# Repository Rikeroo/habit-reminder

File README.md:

# Habit Reminder
Low energy physical habit reminder, using RGB LEDs, a small task screen and tactile switches to build useful habits and get tasks done

## DevBoard Prototype:

## ESP-32 WROOM Board Render:

## Features
- OLED screen to display tasks
- NeoPixel WS281b LED modules to show completion at a glance
- Tactile buttons to complete tasks
## Planned Features
- Integration with ToDoist API, with 2-way sync
- FreeRTOS Implementation for easy scheduling
- Speaker for audible task complete sound
- Enclosure/Stand for flexible display options
- Points/Streaks counter
- LED Integrated buttons? (RBG mech switches)

## Learnt from DevBoard V1 Manufacture and build
- WS2812b fine with 5V supply and 3.3V logic
- Status LED would be usefull for de-bugging
- 4 Pin Female socket for screen would make build easier
- Feet required, or Command strip mounting, or enclosure
- Moving NeoPixels away from screen would make for easier soldering
- Add mounting holes to main pcb for enclosure

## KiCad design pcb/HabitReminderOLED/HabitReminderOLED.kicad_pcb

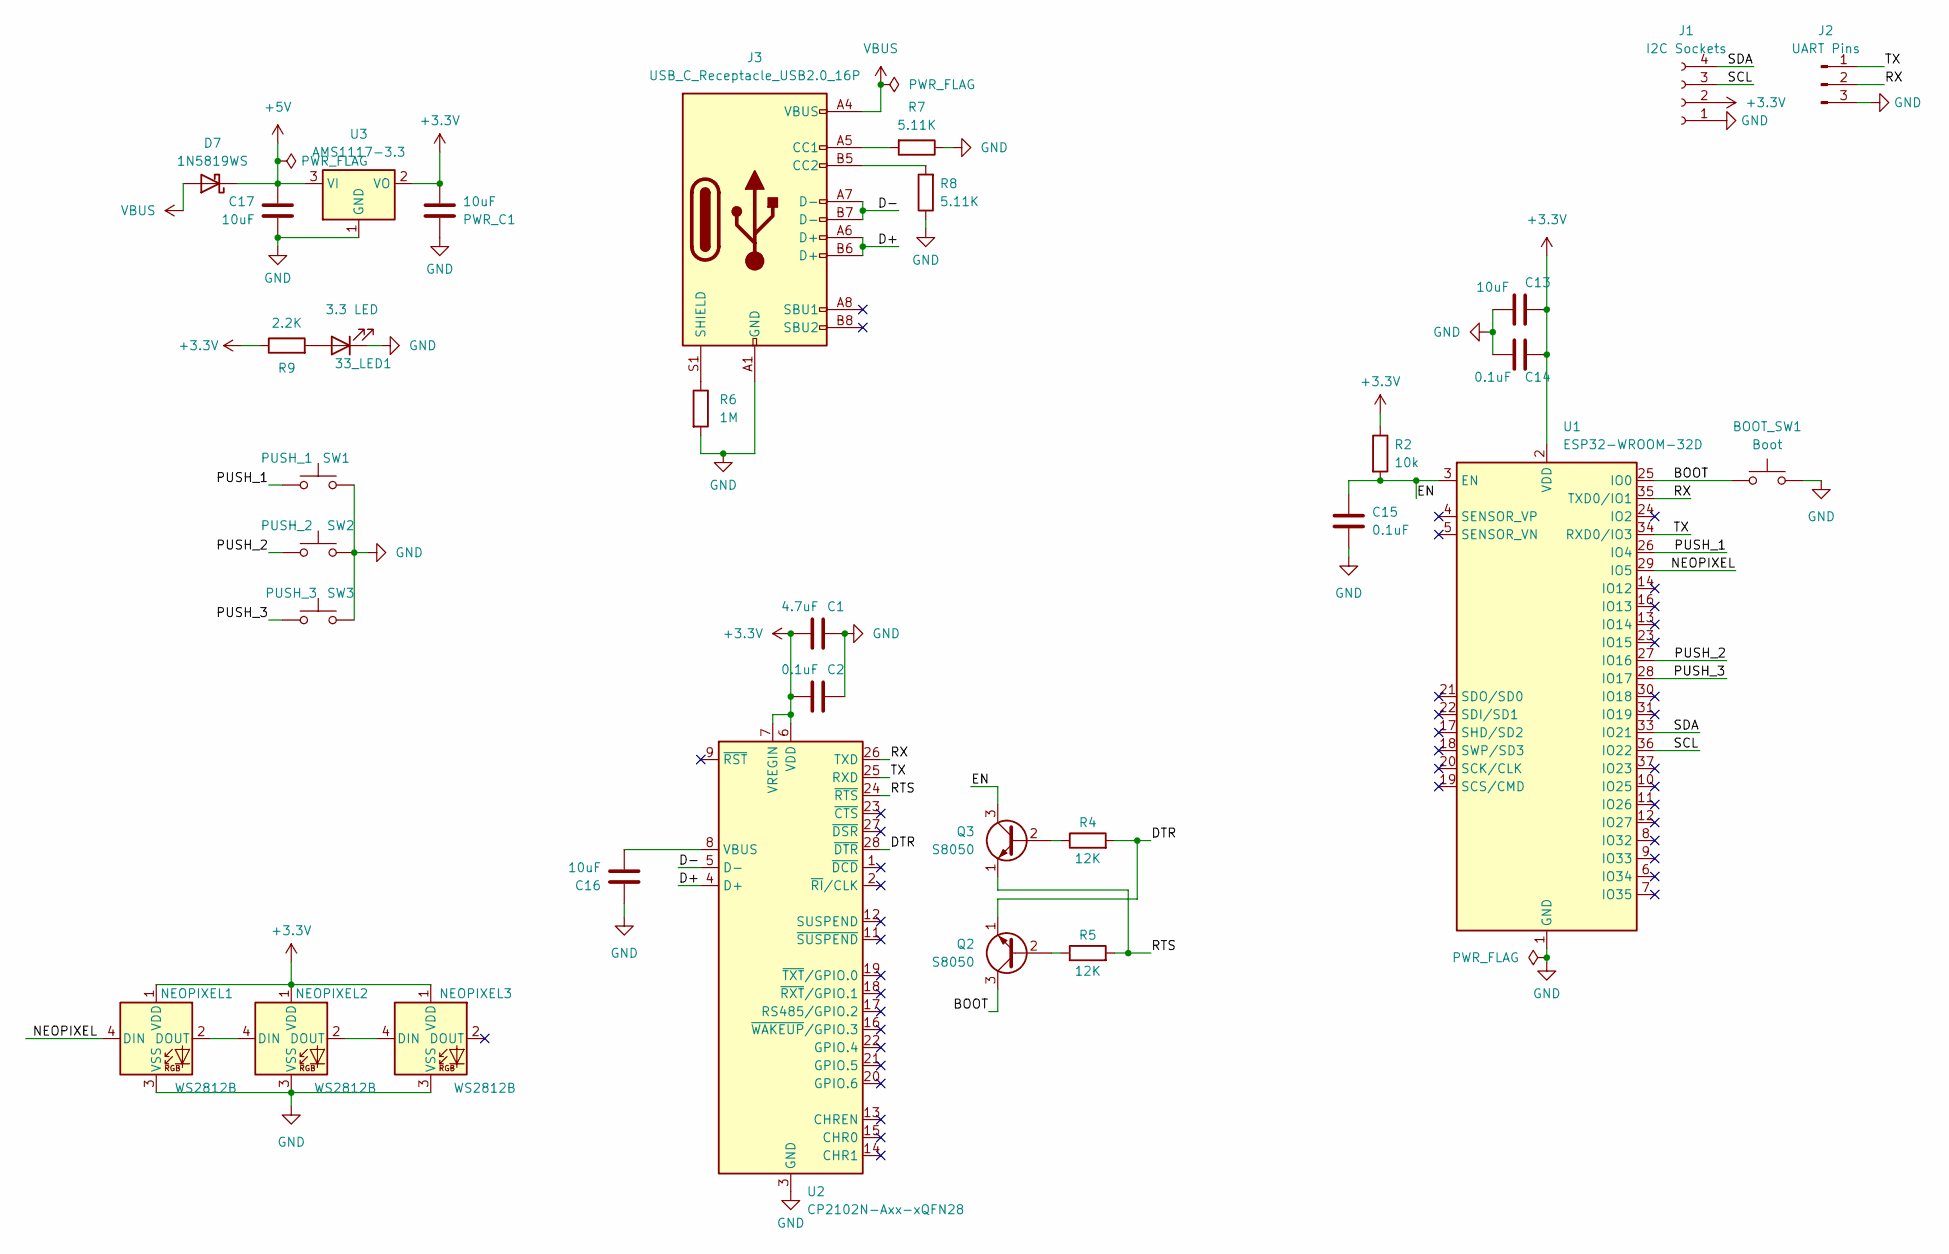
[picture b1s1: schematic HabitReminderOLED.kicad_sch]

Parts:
33_LED1: 3.3 LED; LED_0603_1608Metric; LCSC C965799
BOOT_SW1: Boot; SW_Push_SPST_NO_Alps_SKRK; LCSC C455280
C1: 4.7uF; C_0603_1608Metric; LCSC C1705
C2, C14, C15: 0.1uF; C_0603_1608Metric; LCSC C30926
C13, C16, C17: 10uF; C_0603_1608Metric; LCSC C77044
D7: 1N5819WS; D_SOD-323; LCSC C2828425
J1: I2C Sockets; 128x64OLED_No_Holes; LCSC C2718488
J2: UART Pins; PinHeader_1x03_P2.54mm_Vertical; LCSC C49257
J3: USB_C_Receptacle_USB2.0_16P; USB_C_Receptacle_XKB_U262-16XN-4BVC11; LCSC C319148
NEOPIXEL1, NEOPIXEL2, NEOPIXEL3: WS2812B; LED_WS2812B_PLCC4_5.0x5.0mm_P3.2mm; LCSC C2843785
PWR_C1: 10uF; C_0805_2012Metric; LCSC C15850
Q2, Q3: S8050; SOT-23; LCSC C916390
R2: 10k; R_0603_1608Metric; LCSC C25804
R4, R5: 12K; R_0603_1608Metric; LCSC C114659
R6: 1M; R_0603_1608Metric; LCSC C26098
R7, R8: 5.11K; R_0603_1608Metric; LCSC C2933233
R9: 2.2K; R_0603_1608Metric; LCSC C4190
SW1: PUSH_1; SW_Push_1P1T_NO_6x6mm_H9.5mm; LCSC C455110
SW2: PUSH_2; SW_Push_1P1T_NO_6x6mm_H9.5mm; LCSC C455110
SW3: PUSH_3; SW_Push_1P1T_NO_6x6mm_H9.5mm; LCSC C455110
U1: ESP32-WROOM-32D; LCSC C473012
U2: CP2102N-Axx-xQFN28; QFN-28-1EP_5x5mm_P0.5mm_EP3.35x3.35mm; LCSC C964632
U3: AMS1117-3.3; SOT-223-3_TabPin2; LCSC C347222

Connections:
+3.3V: C1.1, C2.1, C13.2, C14.2, J1.2, NEOPIXEL1.1 (VDD), NEOPIXEL2.1 (VDD), NEOPIXEL3.1 (VDD), PWR_C1.1, R2.1, R9.1, U1.2 (VDD), U2.6 (VDD), U2.7 (VREGIN), U3.2 (VO)
+5V: C17.2, D7.1 (K), U3.3 (VI)
/BOOT: BOOT_SW1.1, Q2.3 (C), U1.25 (IO0)
/D+: J3.A6 (D+), J3.B6 (D+), U2.4 (D+)
/D-: J3.A7 (D-), J3.B7 (D-), U2.5 (D-)
/DTR: Q2.1 (E), R4.2, U2.28 (~DTR)
/EN: C15.2, Q3.3 (C), R2.2, U1.3 (EN)
/NEOPIXEL: NEOPIXEL1.4 (DIN), U1.29 (IO5)
/PUSH_1: SW1.1, U1.26 (IO4)
/PUSH_2: SW2.1, U1.27 (IO16)
/PUSH_3: SW3.1, U1.28 (IO17)
/RTS: Q3.1 (E), R5.2, U2.24 (~RTS)
/RX: J2.2, U1.35 (TXD0/IO1), U2.26 (TXD)
/SCL: J1.3, U1.36 (IO22)
/SDA: J1.4, U1.33 (IO21)
/TX: J2.1, U1.34 (RXD0/IO3), U2.25 (RXD)
GND: 33_LED1.1 (K), BOOT_SW1.2, C1.2, C2.2, C13.1, C14.1, C15.1, C16.1, C17.1, J1.1, J2.3, J3.A1 (GND), J3.A12 (GND), J3.B1 (GND), J3.B12 (GND), NEOPIXEL1.3 (VSS), NEOPIXEL2.3 (VSS), NEOPIXEL3.3 (VSS), PWR_C1.2, R6.2, R7.1, R8.1, SW1.2, SW2.2, SW3.2, U1.1 (GND), U1.15 (GND), U1.38 (GND), U1.39 (GND), U2.3 (GND), U2.29 (GND), U3.1 (GND)
unnamed: 33_LED1.2 (A), R9.2
unnamed: J3.A5 (CC1), R7.2
unnamed: J3.B5 (CC2), R8.2
unnamed: J3.S1 (SHIELD), R6.1
unnamed: NEOPIXEL1.2 (DOUT), NEOPIXEL2.4 (DIN)
unnamed: NEOPIXEL2.2 (DOUT), NEOPIXEL3.4 (DIN)
unnamed: Q2.2 (B), R5.1
unnamed: Q3.2 (B), R4.1
unnamed: C16.2, U2.8 (VBUS)
VBUS: D7.2 (A), J3.A4 (VBUS), J3.A9 (VBUS), J3.B4 (VBUS), J3.B9 (VBUS)

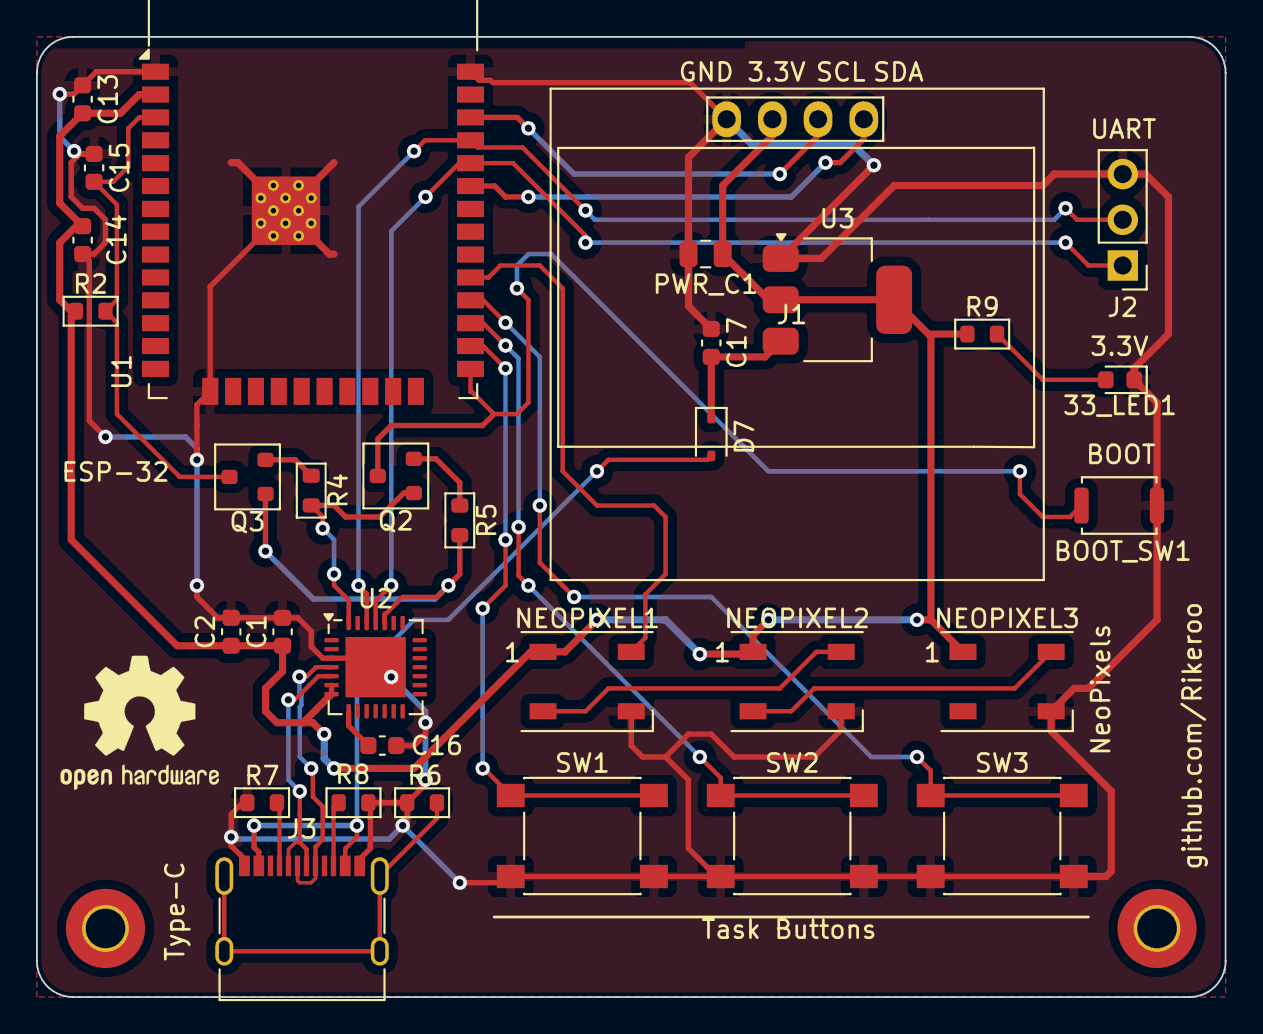
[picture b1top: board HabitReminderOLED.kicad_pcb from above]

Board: 2 copper layers, 66.0 x 53.3 mm, 32 parts (0 on the bottom side), 27 nets.

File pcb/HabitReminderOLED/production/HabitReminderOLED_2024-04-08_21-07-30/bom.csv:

Designator,Footprint,Quantity,Value,LCSC Part #
33_LED1,0603,1,3.3 LED,
BOOT_SW1,SW_Push_SPST_NO_Alps_SKRK,1,Boot,
C1,0603,1,4.7uF,
"C13, C16, C17",0603,3,10uF,
"C14, C15, C2",0603,3,0.1uF,
D7,D_SOD-323,1,1N5819WS,
J1,128x64OLED_No_Holes,1,I2C Sockets,
J2,PinHeader_1x03_P2.54mm_Vertical,1,UART Pins,
J3,USB_C_Receptacle_XKB_U262-16XN-4BVC11,1,USB_C_Receptacle_USB2.0_16P,
"NEOPIXEL1, NEOPIXEL2, NEOPIXEL3",LED_WS2812B_PLCC4_5.0x5.0mm_P3.2mm,3,WS2812B,
PWR_C1,0805,1,10uF,
"Q2, Q3",SOT-23,2,S8050,
R2,0603,1,10k,
"R4, R5",0603,2,12K,
R6,0603,1,1M,
"R7, R8",0603,2,5.11K,
R9,0603,1,2.2K,
SW1,SW_PUSH_6mm,1,PUSH_1,
SW2,SW_PUSH_6mm,1,PUSH_2,
SW3,SW_PUSH_6mm,1,PUSH_3,
U1,ESP32-WROOM-32D,1,ESP32-WROOM-32D,
U2,QFN-28-1EP_5x5mm_P0.5mm_EP3.35x3.35mm,1,CP2102N-Axx-xQFN28,
U3,SOT-223-3_TabPin2,1,AMS1117-3.3,

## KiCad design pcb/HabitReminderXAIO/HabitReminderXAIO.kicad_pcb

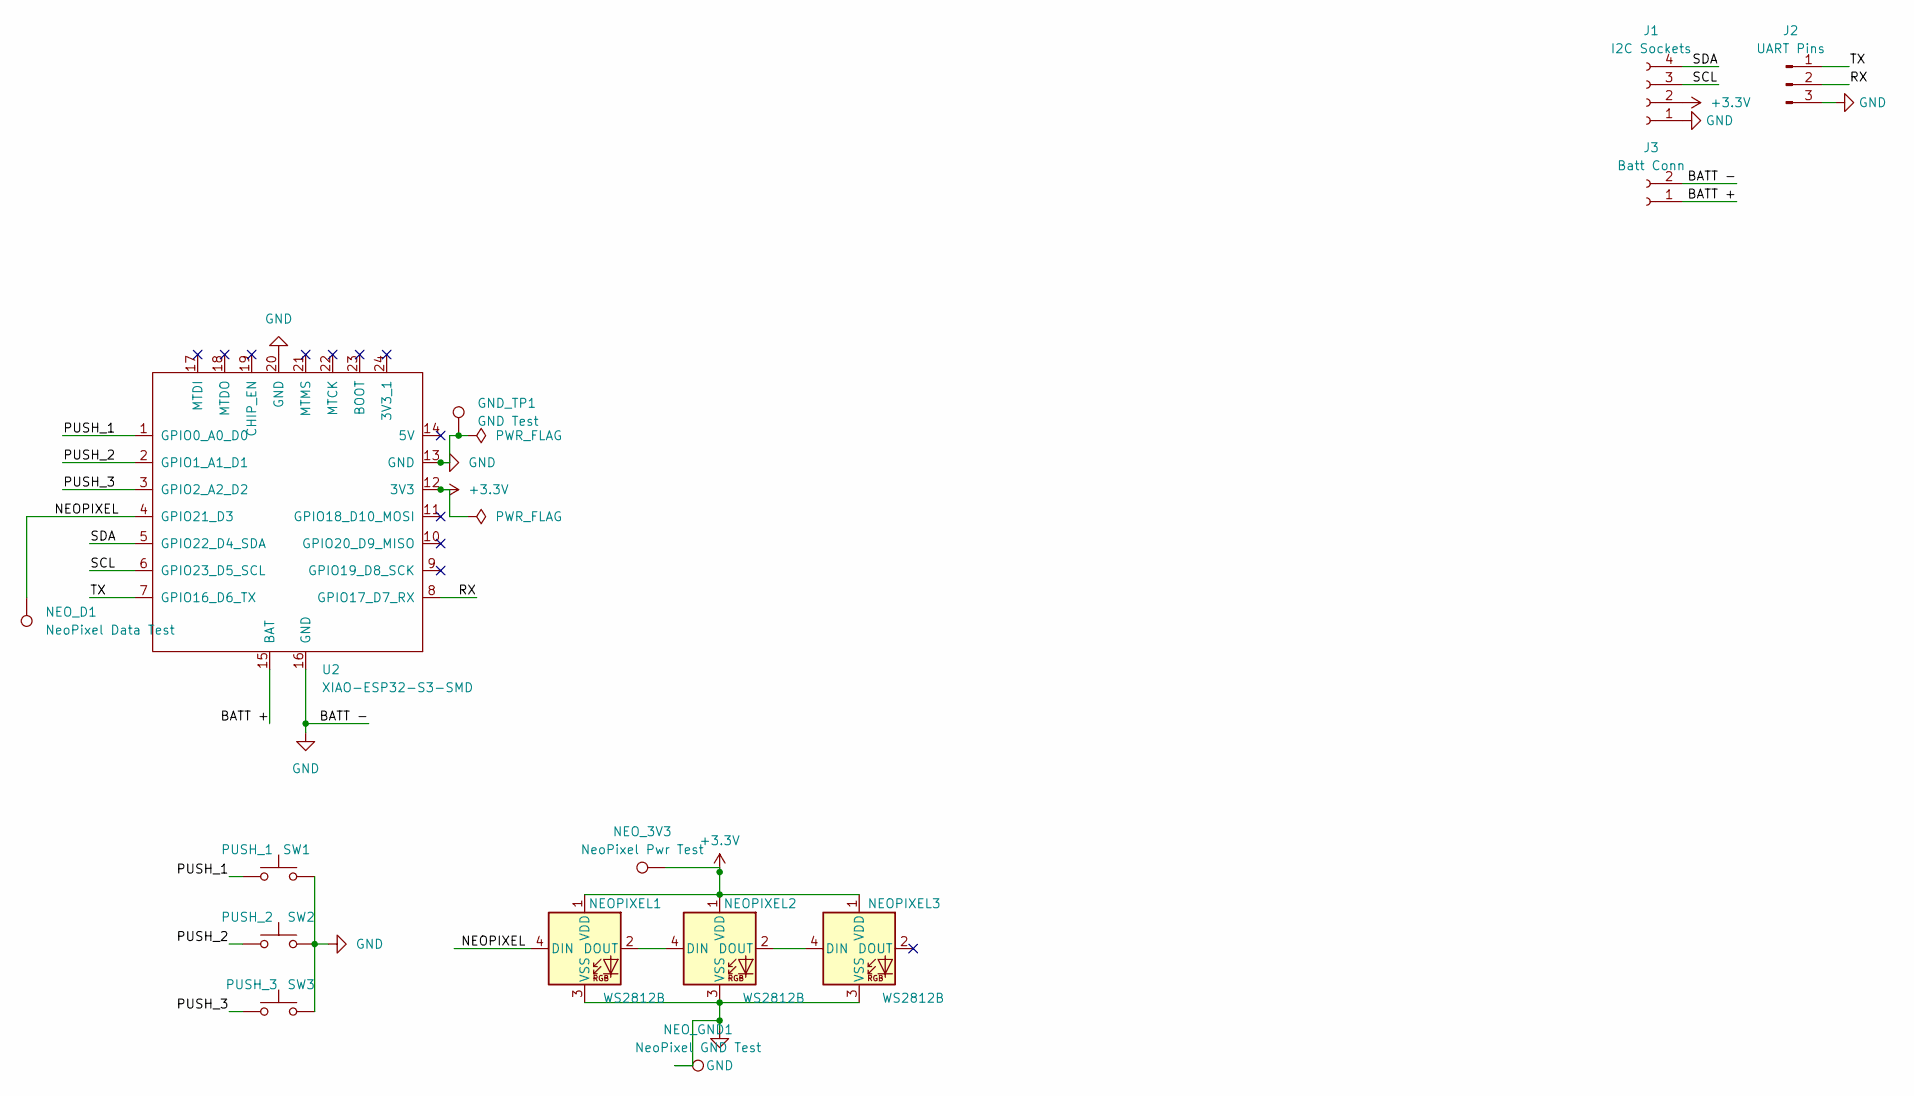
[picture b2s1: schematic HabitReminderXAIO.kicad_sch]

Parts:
GND_TP1: GND Test; TestPoint_Pad_D1.5mm
J1: I2C Sockets; 128x64OLED; LCSC C2718488
J2: UART Pins; PinHeader_1x03_P2.54mm_Vertical; LCSC C49257
J3: Batt Conn; JST_PH_S2B-PH-K_1x02_P2.00mm_Horizontal
NEOPIXEL1, NEOPIXEL2, NEOPIXEL3: WS2812B; LED_WS2812B_PLCC4_5.0x5.0mm_P3.2mm; LCSC C2843785
NEO_3V3: NeoPixel Pwr Test; TestPoint_Pad_D1.5mm
NEO_D1: NeoPixel Data Test; TestPoint_Pad_D1.5mm
NEO_GND1: NeoPixel GND Test; TestPoint_Pad_D1.5mm
SW1: PUSH_1; SW_Push_1P1T_NO_6x6mm_H9.5mm; LCSC C455110
SW2: PUSH_2; SW_Push_1P1T_NO_6x6mm_H9.5mm; LCSC C455110
SW3: PUSH_3; SW_Push_1P1T_NO_6x6mm_H9.5mm; LCSC C455110
U2: XIAO-ESP32-S3-SMD; XIAO-ESP32C6-SMD

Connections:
+3.3V: J1.2, NEOPIXEL1.1 (VDD), NEOPIXEL2.1 (VDD), NEOPIXEL3.1 (VDD), NEO_3V3.1, U2.12 (3V3)
/BATT +: J3.1, U2.15 (BAT)
/NEOPIXEL: NEOPIXEL1.4 (DIN), NEO_D1.1, U2.4 (GPIO21_D3)
/PUSH_1: SW1.1, U2.1 (GPIO0_A0_D0)
/PUSH_2: SW2.1, U2.2 (GPIO1_A1_D1)
/PUSH_3: SW3.1, U2.3 (GPIO2_A2_D2)
/RX: J2.2, U2.8 (GPIO17_D7_RX)
/SCL: J1.3, U2.6 (GPIO23_D5_SCL)
/SDA: J1.4, U2.5 (GPIO22_D4_SDA)
/TX: J2.1, U2.7 (GPIO16_D6_TX)
GND: GND_TP1.1, J1.1, J2.3, J3.2, NEOPIXEL1.3 (VSS), NEOPIXEL2.3 (VSS), NEOPIXEL3.3 (VSS), NEO_GND1.1, SW1.2, SW2.2, SW3.2, U2.13 (GND), U2.16 (GND), U2.20 (GND)
unnamed: NEOPIXEL1.2 (DOUT), NEOPIXEL2.4 (DIN)
unnamed: NEOPIXEL2.2 (DOUT), NEOPIXEL3.4 (DIN)

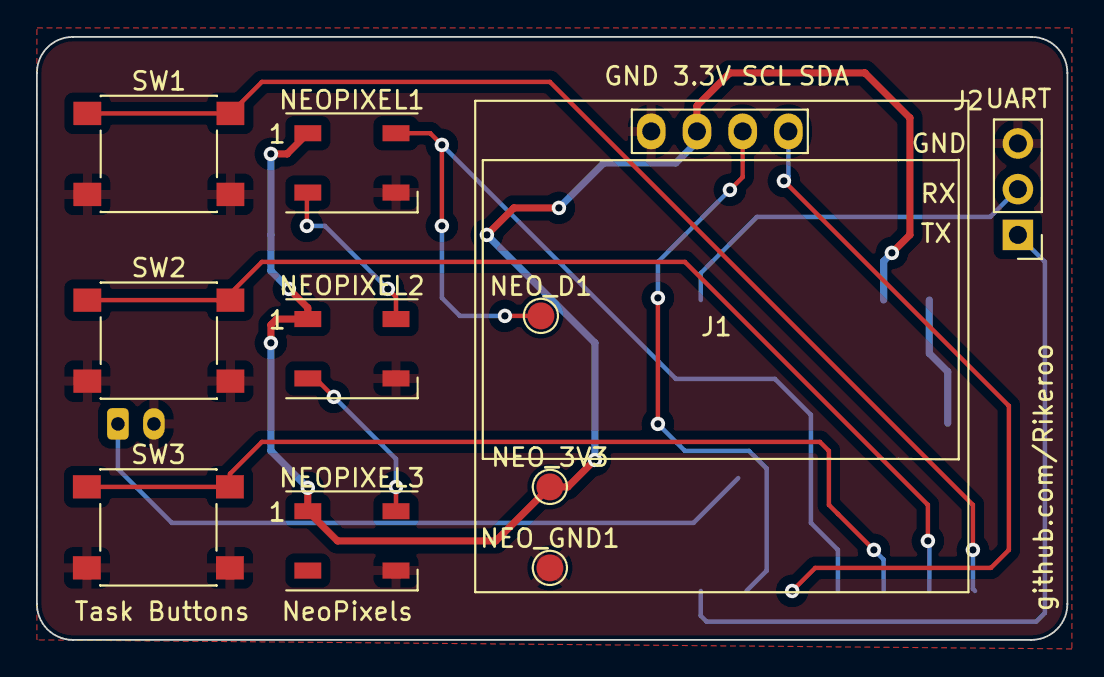
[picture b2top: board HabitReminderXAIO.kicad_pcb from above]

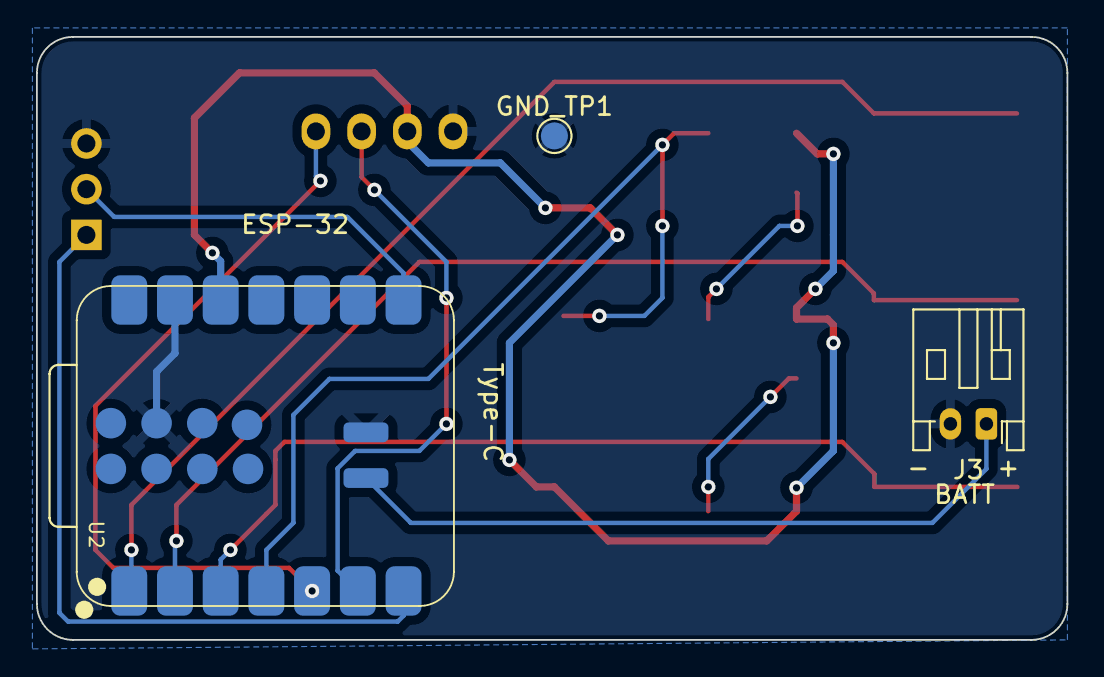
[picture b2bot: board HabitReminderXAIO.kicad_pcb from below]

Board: 2 copper layers, 57.2 x 33.5 mm, 14 parts (3 on the bottom side), 13 nets.

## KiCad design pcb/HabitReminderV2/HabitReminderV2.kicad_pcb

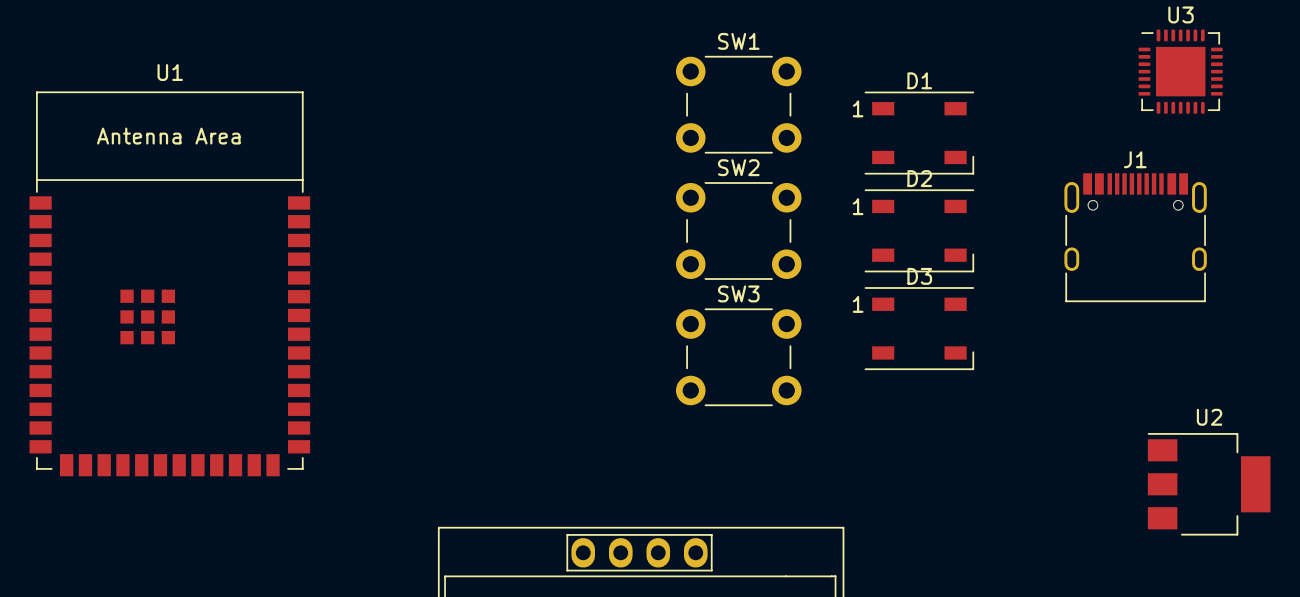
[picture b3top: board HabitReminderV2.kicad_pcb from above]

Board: 2 copper layers, 11 parts (0 on the bottom side), 13 nets, no tracks yet.

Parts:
Brd1: SSD1306; 128x64OLED_No_Holes
D1, D2, D3: WS2812B; LED_WS2812B_PLCC4_5.0x5.0mm_P3.2mm
J1: USB_C_Receptacle_USB2.0; USB_C_Receptacle_HRO_TYPE-C-31-M-12
SW1, SW2, SW3: SW_Push; SW_PUSH_6mm
U1: ESP32-S3-WROOM-1
U2: LD1117S33TR_SOT223; SOT-223-3_TabPin2
U3: CP2102N-Axx-xQFN28; QFN-28-1EP_5x5mm_P0.5mm_EP3.35x3.35mm

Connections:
+5V: Brd1.2 (VCC), D1.1 (VDD), D2.1 (VDD), D3.1 (VDD)
/D+: J1.A6 (D+), J1.B6 (D+), U3.4 (D+)
/D-: J1.A7 (D-), J1.B7 (D-), U3.5 (D-)
/LED: D1.4 (DIN), U1.6 (GPIO6/TOUCH6/ADC1_CH5)
/SCL: Brd1.3 (SCL), U1.11 (GPIO18/U1RXD/ADC2_CH7/CLK_OUT3)
/SDA: Brd1.4 (SDA), U1.10 (GPIO17/U1TXD/ADC2_CH6)
/SW1: SW1.2, U1.21 (GPIO13/TOUCH13/ADC2_CH2/FSPIQ/FSPIIO7/S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)
/SW2: SW2.2, U1.20 (GPIO12/TOUCH12/ADC2_CH1/FSPICLK/FSPIIO6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)
/SW3: SW3.2, U1.19 (GPIO11/TOUCH11/ADC2_CH0/FSPID/FSPIIO5/S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)
GND: Brd1.1 (GND), D1.3 (VSS), D2.3 (VSS), D3.3 (VSS), J1.A1 (GND), J1.A12 (GND), J1.B1 (GND), J1.B12 (GND), J1.S1 (SHIELD), SW1.1, SW2.1, SW3.1, U1.1 (GND), U1.40 (GND), U1.41 (GND), U2.1 (GND), U3.3 (GND), U3.29 (GND)
unnamed: D1.2 (DOUT), D2.4 (DIN)
unnamed: D2.2 (DOUT), D3.4 (DIN)
unnamed: J1.A4 (VBUS), J1.A9 (VBUS), J1.B4 (VBUS), J1.B9 (VBUS)

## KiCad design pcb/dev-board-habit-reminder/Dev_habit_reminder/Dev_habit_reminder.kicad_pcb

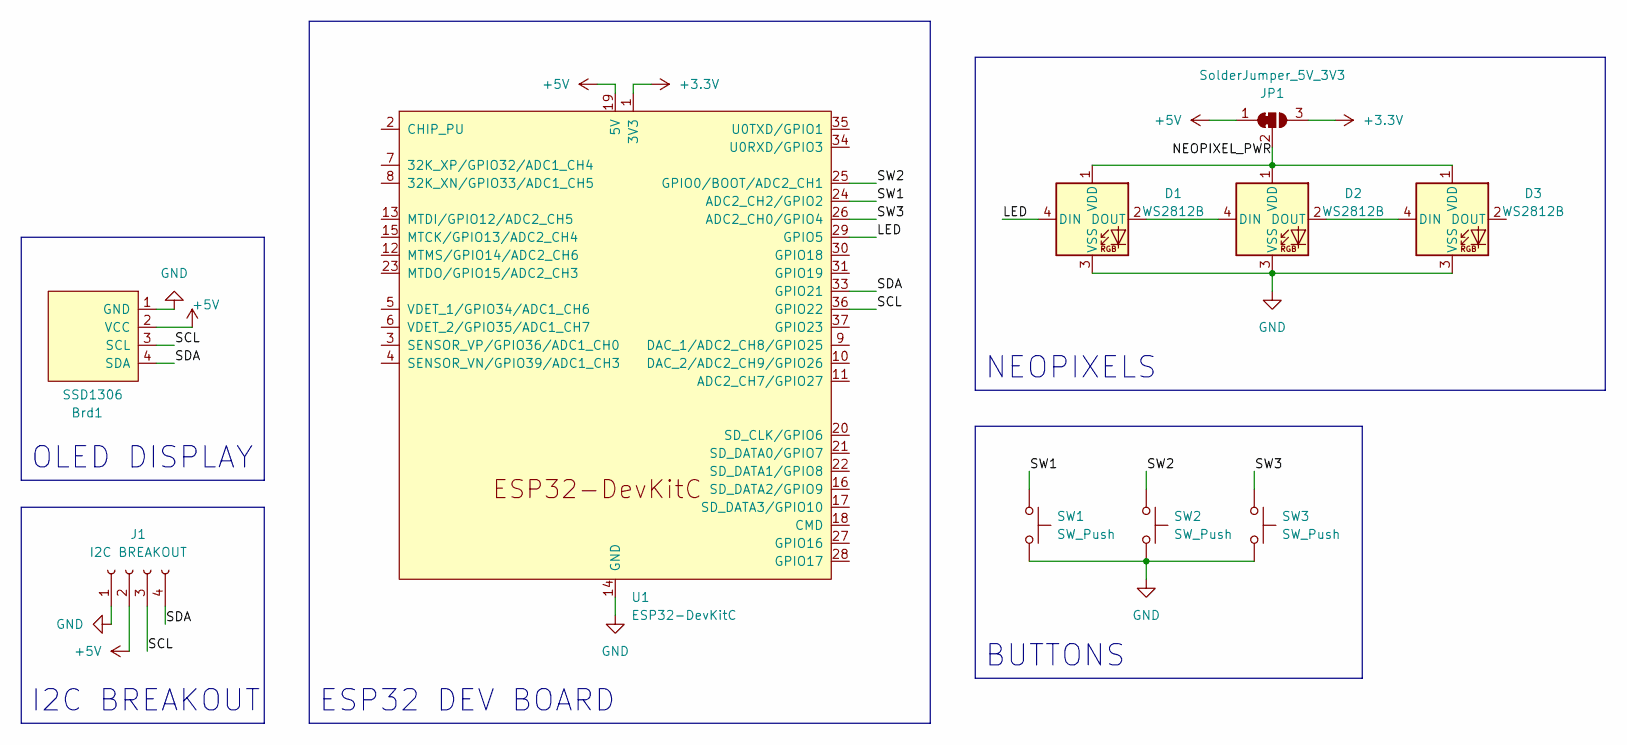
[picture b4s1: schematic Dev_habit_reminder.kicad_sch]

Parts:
Brd1: SSD1306; 128x64OLED_No_Holes
D1, D3: WS2812B; LED_WS2812B_PLCC4_5.0x5.0mm_P3.2mm; MPN C2843785
D2: WS2812B; LED_WS2812B_PLCC4_5.0x5.0mm_P3.2mm
J1: I2C BREAKOUT; PinSocket_1x04_P2.54mm_Vertical
JP1: SolderJumper_5V_3V3; SolderJumper-3_P1.3mm_Bridged12_RoundedPad1.0x1.5mm_NumberL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
SW1, SW2, SW3: SW_Push; SW_PUSH_6mm; MPN C410366
U1: ESP32-DevKitC; ESP32-DevKitC_Shield2

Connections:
+3.3V: JP1.3 (B), U1.1 (3V3)
+5V: Brd1.2 (VCC), J1.2, JP1.1 (A), U1.19 (5V)
/LED: D1.4 (DIN), U1.29 (GPIO5)
/NEOPIXEL_PWR: D1.1 (VDD), D2.1 (VDD), D3.1 (VDD), JP1.2 (C)
/SCL: Brd1.3 (SCL), J1.3, U1.36 (GPIO22)
/SDA: Brd1.4 (SDA), J1.4, U1.33 (GPIO21)
/SW1: SW1.1, U1.24 (ADC2_CH2/GPIO2)
/SW2: SW2.1, U1.25 (GPIO0/BOOT/ADC2_CH1)
/SW3: SW3.1, U1.26 (ADC2_CH0/GPIO4)
GND: Brd1.1 (GND), D1.3 (VSS), D2.3 (VSS), D3.3 (VSS), J1.1, SW1.2, SW2.2, SW3.2, U1.14 (GND), U1.32 (GND), U1.38 (GND)
unnamed: D1.2 (DOUT), D2.4 (DIN)
unnamed: D2.2 (DOUT), D3.4 (DIN)

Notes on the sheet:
I2C BREAKOUT
BUTTONS
ESP32 DEV BOARD
OLED DISPLAY
NEOPIXELS

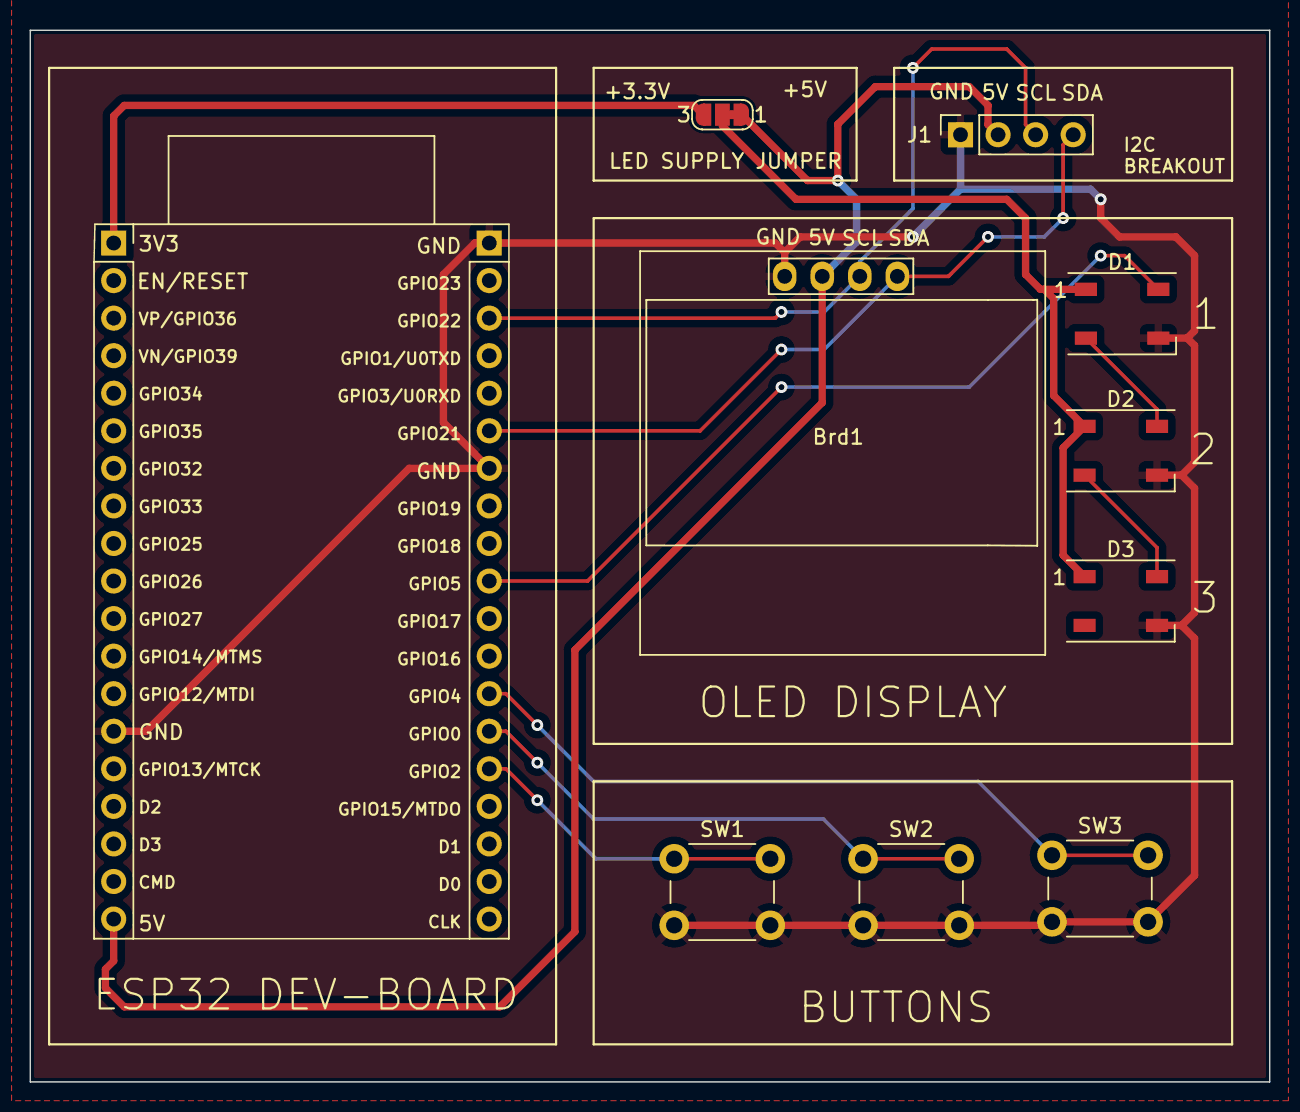
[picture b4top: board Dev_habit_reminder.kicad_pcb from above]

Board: 2 copper layers, 83.8 x 71.1 mm, 10 parts (0 on the bottom side), 12 nets.

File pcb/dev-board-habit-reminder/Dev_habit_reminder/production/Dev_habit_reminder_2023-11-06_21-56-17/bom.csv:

Designator,Footprint,Quantity,Value,LCSC Part #
Brd1,128x64OLED_No_Holes,1,SSD1306,
"D1, D2, D3",LED_WS2812B_PLCC4_5.0x5.0mm_P3.2mm,3,WS2812B,
J1,PinSocket_1x04_P2.54mm_Vertical,1,I2C BREAKOUT,
JP1,SolderJumper-3_P1.3mm_Bridged12_RoundedPad1.0x1.5mm_NumberLabels,1,SolderJumper_5V_3V3,
"SW1, SW2, SW3",SW_PUSH_6mm,3,SW_Push,
U1,ESP32-DevKitC_Shield2,1,ESP32-DevKitC,

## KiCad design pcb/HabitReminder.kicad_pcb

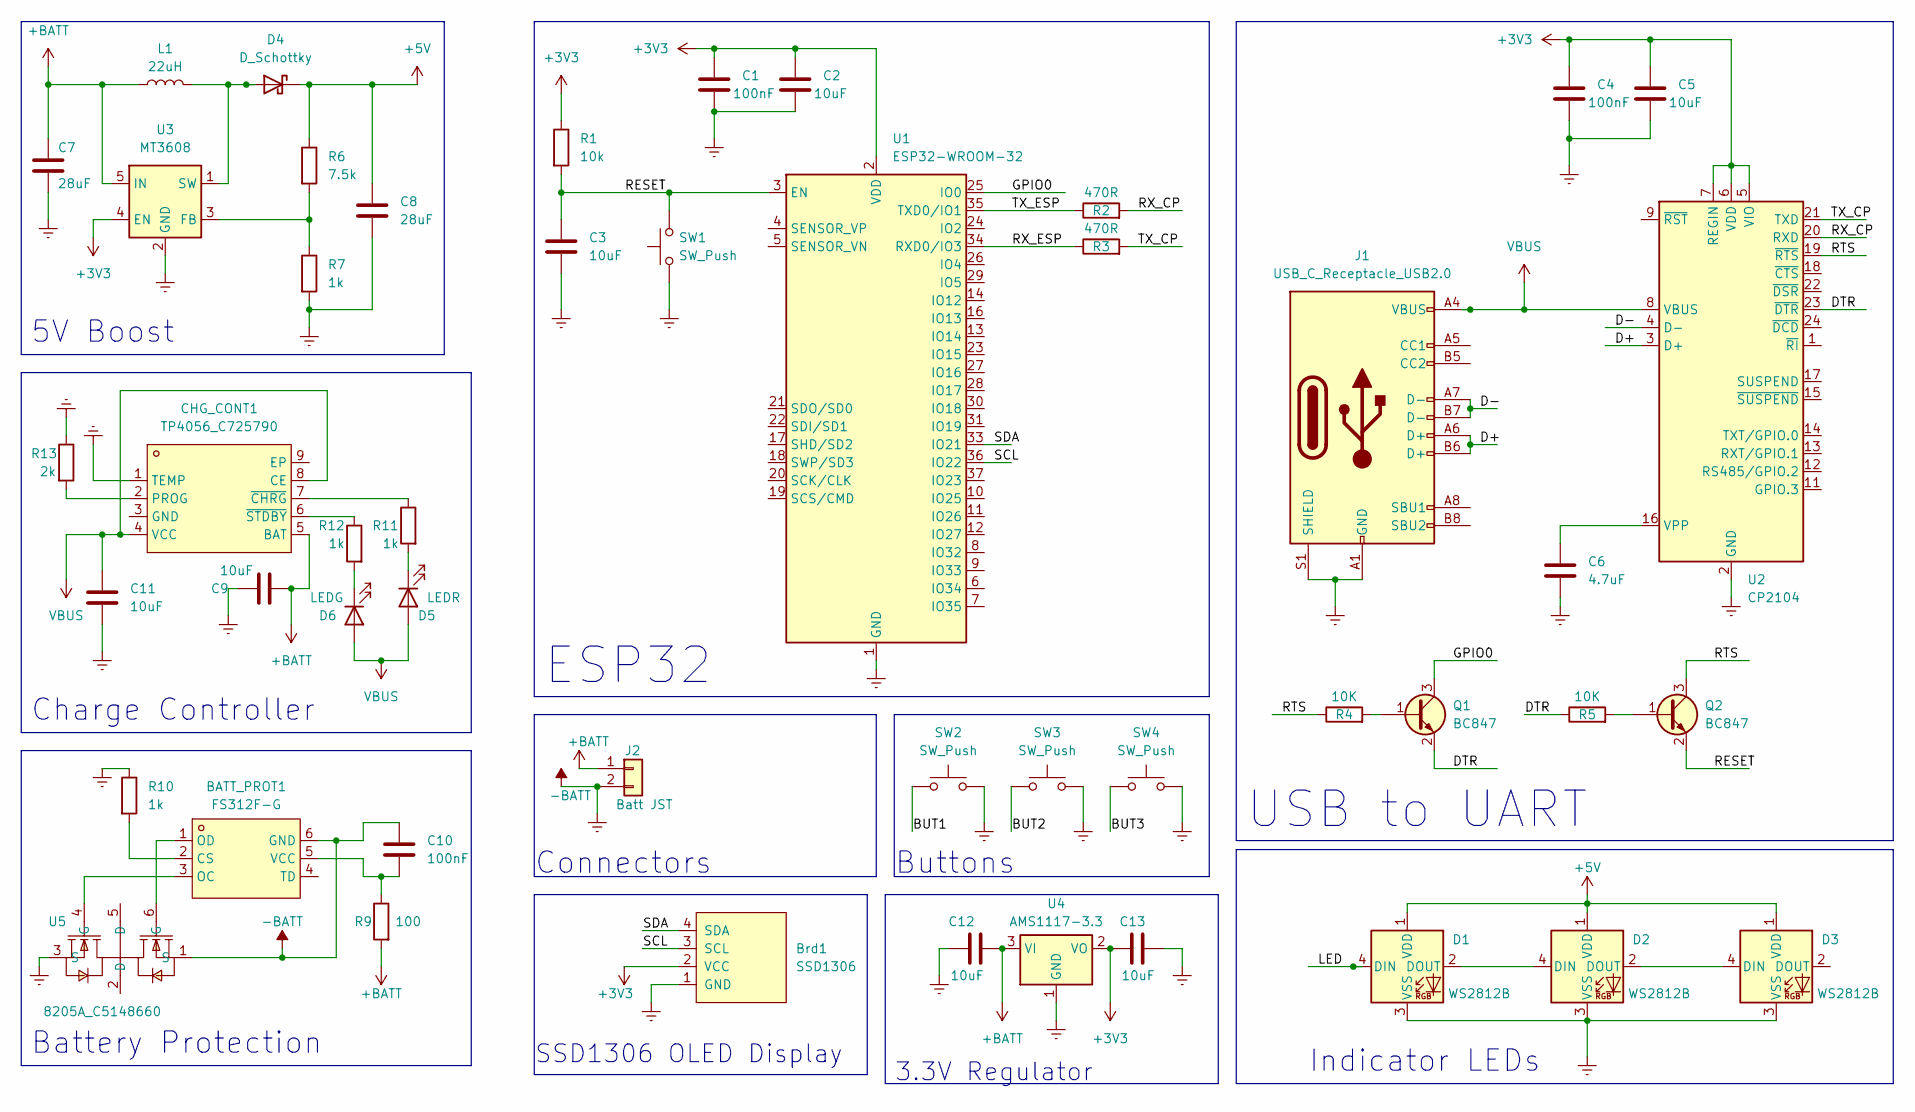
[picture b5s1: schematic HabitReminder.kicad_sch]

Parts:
BATT_PROT1: FS312F-G; SOT-23-6_L2.9-W1.6-P0.95-LS2.8-BR; LCSC Part C82736
Brd1: SSD1306; 128x64OLED
C1, C4, C10: 100nF; C_0805_2012Metric
C2, C3, C5, C9, C11, C12, C13: 10uF; C_0805_2012Metric
C6: 4.7uF; C_0805_2012Metric
C7, C8: 28uF; C_0805_2012Metric
CHG_CONT1: TP4056_C725790; ESOP-8_L4.9-W3.9-P1.27-LS6.0-BL-EP; LCSC Part C725790
D1, D2, D3: WS2812B; LED_WS2812B_PLCC4_5.0x5.0mm_P3.2mm
D4: D_Schottky; D_SOD-523
D5: LEDR; LED_0805_2012Metric
D6: LEDG; LED_0805_2012Metric
J1: USB_C_Receptacle_USB2.0; USB_C_Receptacle_GCT_USB4105-xx-A_16P_TopMnt_Horizontal
J2: Batt JST; R_0805_2012Metric
L1: 22uH; R_0805_2012Metric
Q1, Q2: BC847; SOT-23
R1: 10k; R_0805_2012Metric
R2, R3: 470R; R_0805_2012Metric
R4, R5: 10K; R_0805_2012Metric
R6: 7.5k; R_0805_2012Metric
R7, R10, R11, R12: 1k; R_0805_2012Metric
R9: 100; R_0805_2012Metric
R13: 2k; R_0805_2012Metric
SW1: SW_Push; SW_SPST_TL3305B
SW2, SW3, SW4: SW_Push; SW_PUSH-12mm
U1: ESP32-WROOM-32
U2: CP2104; QFN-24-1EP_4x4mm_P0.5mm_EP2.6x2.6mm
U3: MT3608; SOT-23-6
U4: AMS1117-3.3; SOT-223-3_TabPin2
U5: 8205A_C5148660; SOT-23-6_L2.9-W1.6-P0.95-LS2.8-BR; LCSC Part C5148660

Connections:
+3V3: Brd1.2 (VCC), C1.1, C2.1, C4.1, C5.1, C13.1, R1.1, U1.2 (VDD), U2.5 (VIO), U2.6 (VDD), U2.7 (REGIN), U3.4 (EN), U4.2 (VO)
+5V: C8.1, D1.1 (VDD), D2.1 (VDD), D3.1 (VDD), D4.1 (K), R6.1
+BATT: C7.1, C9.1, C12.2, CHG_CONT1.5 (BAT), J2.1, L1.1, R9.2, U3.5 (IN), U4.3 (VI)
-BATT: BATT_PROT1.6 (GND), Brd1.1 (GND), C1.2, C2.2, C3.2, C4.2, C5.2, C6.2, C7.2, C8.2, C9.2, C10.1, C11.2, C12.1, C13.2, CHG_CONT1.1 (TEMP), D1.3 (VSS), D2.3 (VSS), D3.3 (VSS), J1.A1 (GND), J1.A12 (GND), J1.B1 (GND), J1.B12 (GND), J1.S1 (SHIELD), J2.2, R7.2, R10.1, R13.1, SW1.1, SW2.2, SW3.2, SW4.2, U1.1 (GND), U1.15 (GND), U1.38 (GND), U1.39 (GND), U2.2 (GND), U2.25 (GND), U3.2 (GND), U4.1 (GND), U5.1 (S), U5.3 (S)
/BUT1: SW2.1
/BUT2: SW3.1
/BUT3: SW4.1
/D+: J1.A6 (D+), J1.B6 (D+), U2.3 (D+)
/D-: J1.A7 (D-), J1.B7 (D-), U2.4 (D-)
/DTR: Q1.2 (E), R5.1, U2.23 (~DTR)
/GPIO0: Q1.3 (C), U1.25 (IO0)
/LED: D1.4 (DIN)
/RESET: C3.1, Q2.2 (E), R1.2, SW1.2, U1.3 (EN)
/RTS: Q2.3 (C), R4.1, U2.19 (~RTS)
/RX_CP: R2.2, U2.20 (RXD)
/RX_ESP: R3.1, U1.34 (RXD0/IO3)
/SCL: Brd1.3 (SCL), U1.36 (IO22)
/SDA: Brd1.4 (SDA), U1.33 (IO21)
/TX_CP: R3.2, U2.21 (TXD)
/TX_ESP: R2.1, U1.35 (TXD0/IO1)
unnamed: BATT_PROT1.2 (CS), R10.2
unnamed: BATT_PROT1.3 (OC), U5.4 (G)
unnamed: BATT_PROT1.1 (OD), U5.6 (G)
unnamed: BATT_PROT1.5 (VCC), C10.2, R9.1
unnamed: CHG_CONT1.2 (PROG), R13.2
unnamed: CHG_CONT1.7 (~CHRG), R11.1
unnamed: CHG_CONT1.6 (~STDBY), R12.1
unnamed: D1.2 (DOUT), D2.4 (DIN)
unnamed: D2.2 (DOUT), D3.4 (DIN)
unnamed: D4.2 (A), L1.2, U3.1 (SW)
unnamed: D5.1 (K), R11.2
unnamed: D6.1 (K), R12.2
unnamed: Q1.1 (B), R4.2
unnamed: Q2.1 (B), R5.2
unnamed: C6.1, U2.16 (VPP)
unnamed: R6.2, R7.1, U3.3 (FB)
VBUS: C11.1, CHG_CONT1.4 (VCC), CHG_CONT1.8 (CE), D5.2 (A), D6.2 (A), J1.A4 (VBUS), J1.A9 (VBUS), J1.B4 (VBUS), J1.B9 (VBUS), U2.8 (VBUS)

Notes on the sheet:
Buttons
Charge Controller
USB to UART
Indicator LEDs
ESP32
3.3V Regulator
5V Boost
Battery Protection
SSD1306 OLED Display
Connectors

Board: 2 copper layers, 48 parts (0 on the bottom side), 33 nets, no tracks yet.

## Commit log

2023-10-27 Create habit_reminder.ino
    Initial arduino sketch upload. Updated crosses to be drawn with u8g2.drawGlyph instead of drawline
2023-10-27 Clean up repo structure
2023-10-27 Schematic with 3.3V LDO and OLED display
2023-10-27 Cleanup folder structure
2023-10-28 OOP Implementation
2023-10-28 Fully working basic firmware
    Menu with single button (short and long press) navigation. Using an array of objects for tasks, with appropriate functions for getting and changing attributes.
2023-10-28 Formatting
2023-10-28 Add multi button support
2023-10-29 working with 3 single colour LEDs
    220 ohm resistors
2023-10-30 Added ntp time syncing
2023-10-30 Started switch to Platform IO
2023-10-30 Change to previous version due to error
    Error in touch module
2023-11-06 NeoPixel Implementation, Dev Board PCB V1
2023-11-06 PCB Track width definition, rerouting
2023-11-06 Added ground area and production files
2023-11-08 Board re-routing
2023-11-08 Changed button pins for efficient routing
2023-11-08 Start on V2 main-board and USB to UART
2023-11-09 Backup
2023-11-19 Working firmware for devboard v1
2023-11-19 Add prototype image
2023-11-19 Image resize, feature list
2023-11-19 schematic updates
2024-01-18 Spelling error fix
2024-03-26 E-paper initial design, connector
2024-04-03 Epaper initial prototype. Still needs main user buttons footprints
2024-04-07 inital E-Paper prototype, OLED inital board finished
2024-04-07 Create OLED Board Render
2024-04-07 Update OLED Board Render
2024-04-08 Move to SMD buttons, added LCSC designators
2025-02-19 Updated OLED Board and created XAIO based board
2025-02-19 Initial platformio project
2025-02-21 inital esp32 blink example
2025-02-21 working blinking on esp32-c6 xaio
2025-02-21 Flashing neo-pixel LEDs
2025-02-21 example SSD1306 display code ported - not yet tested
2025-03-01 WIP: Moving functionality to seperate files for OLED screen and LED strip
2025-03-01 Moved OLED and NeoPixel LED functionality to own components
2025-03-02 Switched to RMT for LED strip control due to issues with SPI. Tested and working reliably on breadboard
2025-03-02 Removed unnecessary waiting and neopixel inital refreshing and re-instated OLED display demo. Confirmed both working
2025-03-09 Flipped display and changed LED colour - working on new PCB
2025-03-10 Semi-working task display - LEDs responding correctly to button inputs
2025-04-14 Removed now irrelevant README
2025-07-09 Smaller fonts and changed spacing of checkbox items
2025-07-09 Using flex-containers for better spacing of task check-boxes
